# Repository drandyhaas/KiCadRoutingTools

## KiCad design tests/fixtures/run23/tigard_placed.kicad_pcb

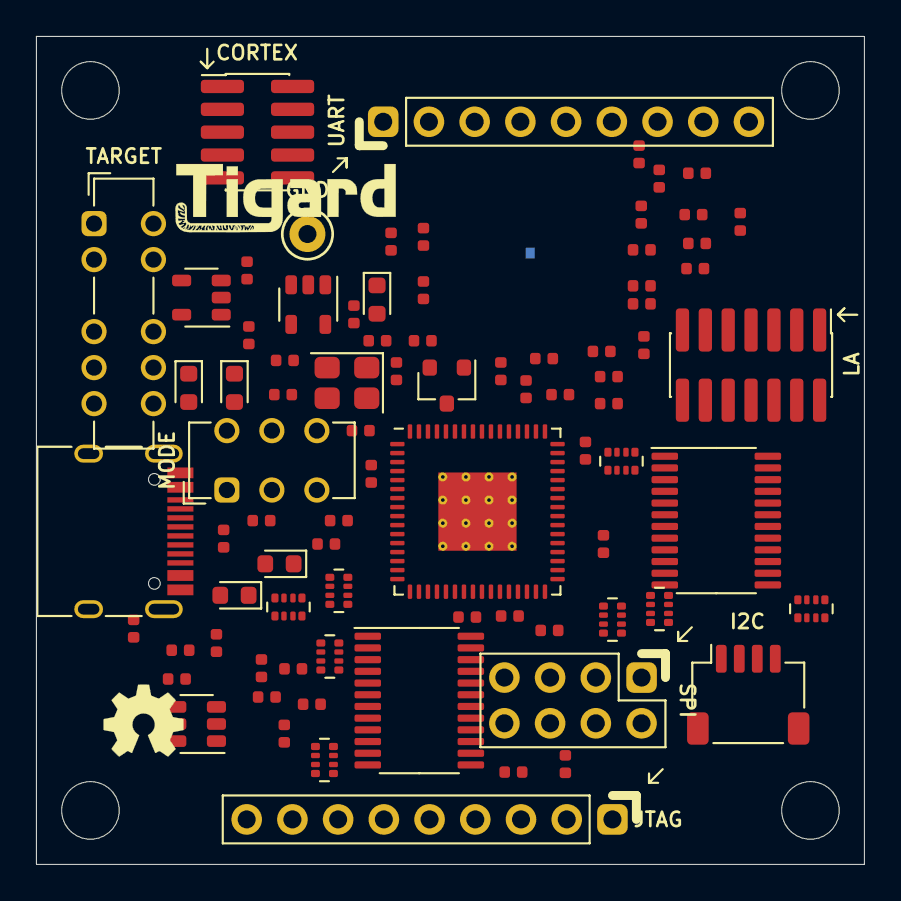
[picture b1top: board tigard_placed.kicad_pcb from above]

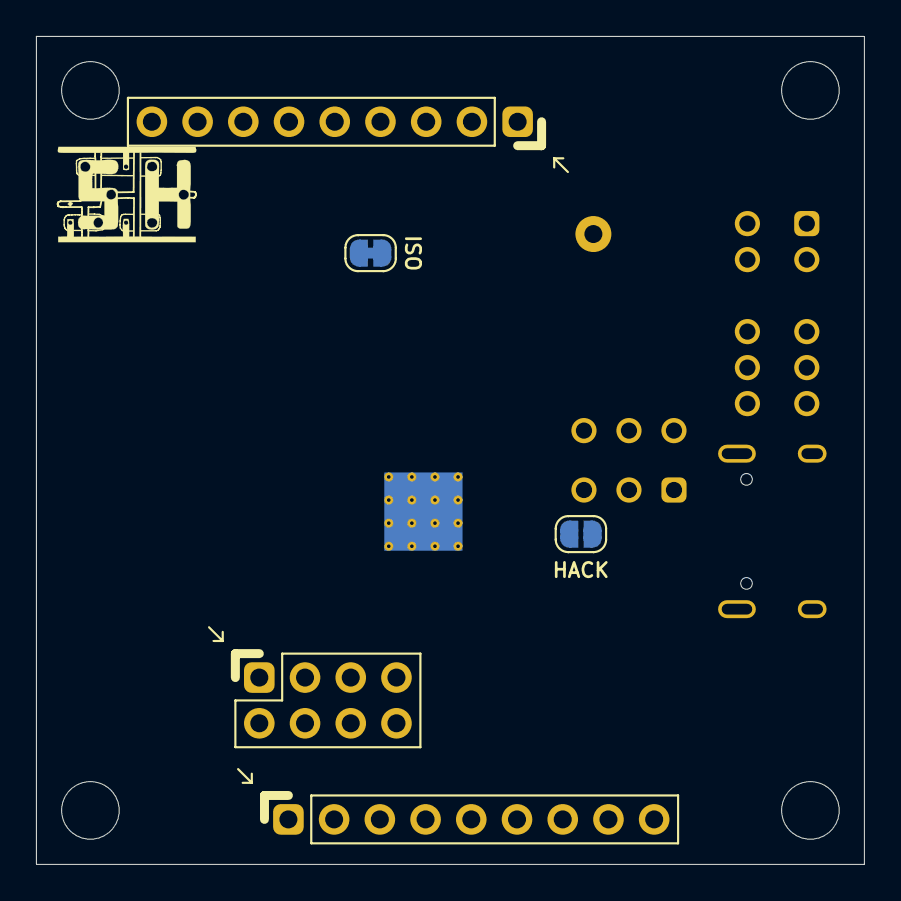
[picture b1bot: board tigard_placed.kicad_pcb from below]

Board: 4 copper layers, 46.0 x 46.0 mm, 91 parts (3 on the bottom side), 85 nets, no tracks yet.

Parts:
C1, C2, C3, C4, C6, C7, C9, C10: 2u2; C_0402_1005Metric
C5, C8, C11, C12, C13, C14, C15, C16, C17, C18, C19, C20, C21, C22, C26: 100n; C_0402_1005Metric
C23, C24: 30pF; C_0402_1005Metric
C25: NF; C_0402_1005Metric
D1, D4: YELLOW; LED_0603_1608Metric
D2: BLUE; LED_0603_1608Metric
D3, D5: GREEN; LED_0603_1608Metric
FB1, FB2, FB3: 600R, 0.5A; L_0402_1005Metric
H1, H2, H3, H4: MountingHole; MountingHole_3.2mm_M3_ISO7380
J1: USB_C_Receptacle_USB2.0; USB_C_Receptacle_HRO_TYPE-C-31-M-12
J2: JTAG; PinHeader_1x09_P2.54mm_Vertical
J3: UART; PinHeader_1x09_P2.54mm_Vertical
J4: SPI; PinHeader_2x04_P2.54mm_Vertical
J5: CORTEX; PinHeader_2x05_P1.27mm_Vertical_SMD
J6: LA; PinHeader_2x07_P1.27mm_Vertical_SMD
J7: I2C; JST_SH_SM04B-SRSS-TB_1x04-1MP_P1.00mm_Horizontal
JP1: ISO; SolderJumper-2_P1.3mm_Bridged_RoundedPad1.0x1.5mm
JP2: HACK; SolderJumper-2_P1.3mm_Open_RoundedPad1.0x1.5mm
LOGO1: Logo_Open_Hardware_Small; OSHW-Symbol_4.4x4mm_SilkScreen
LOGO2: Logo_SH; Securing_Hardware_Logo
Q1: BSH103; SOT-23_RoundRect
R1, R2: 5k1; R_0402_1005Metric
R3, R17: 1M; R_0402_1005Metric
R4, R5, R8, R9, R11, R16: 330; R_0402_1005Metric
R6: 12k, 1%; R_0402_1005Metric
R7, R10, R12, R13, R14, R18, R19, R20, R21, R24: 10k; R_0402_1005Metric
R15: 2.2k; R_0402_1005Metric
R22: 2k2; R_0402_1005Metric
RN1, RN2, RN7, RN8: 100k; R_Array_Convex_4x0402_RoundRect
RN3, RN4, RN5, RN6: 100; R_Array_Convex_4x0402_RoundRect
SW1: TARGET; SW_ALPS_SSSS224100_DP4T
SW2: MODE; SW_CuK_JS202011CQN_DPDT_Straight
TP1: GND; TestPoint_Keystone_5000-5004_Miniature
U1: AP7365-18; SOT-23-5_RoundRect
U2: AP7365-33; SOT-23-5_RoundRect
U3: FT2232HQ; QFN-64-1EP_9x9mm_P0.5mm_EP4.35x4.35mm_ThermalVias
U4: 93LC46BT-I/OT; SOT-23-6_RoundRect
U5, U6: SN74LVC8T245; TSSOP-24_4.4x7.8mm_P0.65mm
Y1: 12MHz; Crystal_SMD_3225-4Pin_3.2x2.5mm_RoundRect

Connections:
+1V8: C2.1, SW1.9, U1.5
+3V3: C4.1, C14.1, C15.1, C16.1, C17.1, C18.1, C19.1, C20.1, FB1.1, FB2.1, R4.1, R5.1, R7.1, R8.2, R9.2, R10.1, R11.2, R12.1, R13.1, R14.1, R18.1, RN1.1, RN1.2, RN1.3, RN1.4, RN2.1, RN2.2, RN2.3, RN2.4, SW1.7, U2.5, U3.20, U3.31, U3.42, U3.50, U3.56, U4.6, U5.1, U6.1
+5V: C1.1, C3.1, C26.1, FB3.1, SW1.6, U1.1, U1.3, U2.1, U2.3
/AD0: RN2.5, U3.16, U5.10
/AD1: RN5.1, U3.17
/AD2: RN2.6, U3.18, U5.9
/AD3: RN5.2, U3.19
/AD4: RN2.7, U3.21, U5.8
/AD5: RN5.3, U3.22
/AD6: RN5.4, U3.23
/BD0: RN1.8, U3.38, U5.3
/BD1: RN1.7, U3.39, U5.4
/BD2: RN6.1, U3.40
/BD3: RN1.6, U3.41, U5.5
/BD4: RN1.5, U3.43, U5.6
/BD5: R22.1, RN2.8, U3.44, U5.7
/BD6: RN6.2, U3.45
/BD7: R22.2, U3.46
/CIPO: J2.5, J4.3, J5.6, SW2.4
/CLK: J2.3, J4.6, J5.4, J6.1, J7.4, RN3.8
/COPI: J2.4, J4.8, J5.8, J6.2, J7.3, JP2.1, R16.2, RN3.7
/CORTEX_PIN2: J5.2, SW2.2
/CS: J2.6, J4.1, J6.4, RN3.6, SW2.1
/DI: J6.3, RN8.1, SW2.5, U6.17
/EECLK: R14.2, U3.62, U4.4
/EECS: R12.2, U3.63, U4.5
/EEDATA: R15.1, U3.61, U4.3
/ICE_CDONE: J2.9, J3.4, J6.8, RN7.1, RN8.2, U6.16, U6.21
/RXLED: D3.1, U3.29
/SWDIO: JP2.2, R16.1, SW2.3, SW2.6
/TXLED: D4.1, U3.30
/UART_TX: J3.3, J6.7, RN4.5
/USB_DN: J1.A7, J1.B7, U3.7
/USB_DP: J1.A6, J1.B6, U3.8
/VBUS: FB3.2, J1.A4, J1.A9, J1.B4, J1.B9
/VPHY: C5.1, C6.1, FB1.2, U3.4
/VPLL: C7.1, C8.1, FB2.2, U3.9
/xPB4: J2.7, J6.5, RN3.5
/xPB5: J2.8, J5.10, J6.6, RN4.8
/~ENABLE: D5.1, R10.2, U3.60, U5.22, U6.22
/~UART_CTS: J3.6, RN7.2, U6.20
/~UART_DCD: J3.9, RN7.4, U6.18
/~UART_DSR: J3.8, RN7.3, U6.19
/~UART_DTR: J3.7, RN4.7
/~UART_RTS: J3.5, RN4.6
GND: C1.2, C2.2, C3.2, C4.2, C5.2, C6.2, C7.2, C8.2, C9.2, C10.2, C11.2, C12.2, C13.2, C14.2, C15.2, C16.2, C17.2, C18.2, C19.2, C20.2, C21.2, C22.2, C23.2, C24.2, C25.1, C26.2, D1.1, J1.A1, J1.A12, J1.B1, J1.B12, J2.2, J3.2, J4.7, J5.3, J5.5, J5.9, J6.9, J6.10, J7.1, J7.MP, Q1.2, R1.1, R2.2, R3.1, R6.1, R17.2, R19.2, R24.1, TP1.1, U1.2, U2.2, U3.1, U3.5, U3.10, U3.11, U3.13, U3.15, U3.25, U3.35, U3.47, U3.51, U3.65, U4.2, U5.11, U5.12, U5.13, U6.11, U6.12, U6.13, Y1.2, Y1.4
unnamed: C23.1, U3.2, Y1.1
unnamed: C24.1, U3.3, Y1.3
unnamed: C25.2, J1.S1, R3.2
unnamed: D1.2, R4.2
unnamed: D2.1, Q1.3
unnamed: D2.2, R5.2
unnamed: D3.2, R8.1
unnamed: D4.2, R9.1
unnamed: D5.2, R11.1
unnamed: J1.A5, R1.2
unnamed: J1.B5, R2.1
unnamed: J4.4, R21.2
unnamed: J4.5, R20.1
unnamed: R6.2, U3.6
unnamed: R7.2, U3.14
unnamed: R13.2, R15.2, U4.1
unnamed: R18.2, U5.2
unnamed: R19.1, U6.2
unnamed: RN3.1, U5.21
unnamed: RN3.2, U5.20
unnamed: RN3.3, U5.19
unnamed: RN3.4, U5.18
unnamed: RN4.1, U5.17
unnamed: RN4.2, U5.16
unnamed: RN4.3, U5.15
unnamed: RN4.4, U5.14
unnamed: RN5.5, U6.6
unnamed: RN5.6, U6.5
unnamed: RN5.7, U6.4
unnamed: RN5.8, U6.3
unnamed: RN6.5, U6.10
unnamed: RN6.6, U6.9
unnamed: RN6.7, U6.8
unnamed: RN6.8, U6.7
unnamed: RN8.3, U6.15
unnamed: RN8.4, U6.14
VREF: C21.1, C22.1, JP1.2, Q1.1, R17.1, R24.2, RN7.5, RN7.6, RN7.7, RN7.8, RN8.5, RN8.6, RN8.7, RN8.8, SW1.8, U5.23, U5.24, U6.23, U6.24
VREG: C9.1, C10.1, C11.1, C12.1, C13.1, U3.12, U3.37, U3.49, U3.64
VTARGET: J2.1, J3.1, J4.2, J5.1, J7.2, JP1.1, R20.2, R21.1, SW1.10

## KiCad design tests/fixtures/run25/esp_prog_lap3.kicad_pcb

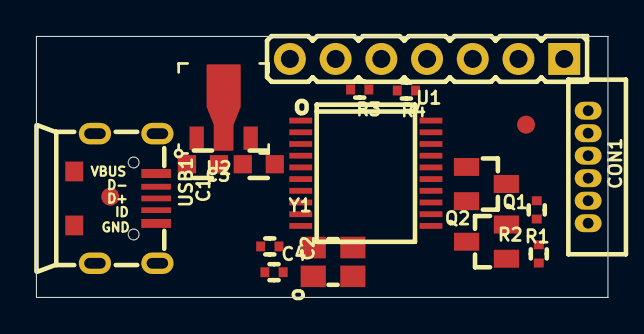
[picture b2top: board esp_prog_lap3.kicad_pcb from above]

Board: 2 copper layers, 31.8 x 14.5 mm, 18 parts (0 on the bottom side), 17 nets, no tracks yet.

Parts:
C1, C3: 2.2uF; C_0603_5MIL_DWS
C2, C4: 27pF; C_0402_5MIL_DWS
CON1: CON6; WU06SM
CON2: CON6; HN1x7
Q1, Q2: BC817-40(SOT23); SOT23
R1, R2: 1K; R_0402_5MIL_DWS
R3, R4: 100R; R_0402_5MIL_DWS
Ref*: Val**; Fiducial1x3_transp
Ref*#2: Val**; Fiducial1x3_transp
U1: CH340H/T; SSOP-20W
U2: ME6210-SOT89; SOT89
USB1: USB-uicro-B; USB-MICRO_MISB-SWMM-5B_LF
Y1: Q12MHz/20pF/10ppm/4P/3.2x2.5mm; TSX-3.2x2.5mm_GND(3)

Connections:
/+3.3V: C3.1, CON1.5, CON2.5, U1.5, U1.19, U2.3
/DCOM: CON1.2, CON2.2, Q1.3
/DTR: Q1.2, R2.2, U1.15
/D_N: U1.7, USB1.2
/D_P: U1.6, USB1.3
/EN: CON1.6, CON2.6, Q2.3
/RTS: Q2.2, R1.2, U1.16
/U0RXD: CON1.3, CON2.3, R3.1
/U0TXD: CON1.1, CON2.1, R4.1
GND: C1.2, C2.2, C3.2, C4.2, CON1.4, CON2.4, U1.8, U2.1, USB1.0, USB1.5, Y1.3
unnamed: C1.1, CON2.7, U2.2, USB1.1
unnamed: C2.1, U1.10, Y1.2
unnamed: C4.1, U1.9, Y1.1
unnamed: Q1.1, R1.1
unnamed: Q2.1, R2.1
unnamed: R3.2, U1.3
unnamed: R4.2, U1.4

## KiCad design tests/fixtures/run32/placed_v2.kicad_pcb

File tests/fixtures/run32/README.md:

# run32 fixtures: run 32's placed glasgow_revC

Copied from `repro/run32/` on `edgehero/KiCadRoutingTools@run32-assets`, the assets #1031 was filed against. That run's work directory (`wk/run32/`) is gitignored, so the test that pins #1031 on this board used to self-skip on every clone, and no machine had the board.

| file | what it is | sha256 (of the committed LF bytes) |
|---|---|---|
| `placed_v2.kicad_pcb` | glasgow_revC as run 32's placement left it, unrouted. Its rule area is a ~1.7 mm no-track, no-via band round the outline on F.Cu and B.Cu, with parts seated against it | `ce68fd39…6514` |
| `placed_v2.kicad_pro` | its project sibling (carries the DRC floor; never copy a board without it) | `488b5933…a714` |

Reader: `test_1031_keepout_run32_repro`. It checks that the pad-legality grader names exactly the parts whose pads no track can reach through that band (C89, D12, R11, R12, U14, U9), and that it does not name D4, D6, D11 or U31, whose pads sit near the band but connected when each net was routed alone on this board.

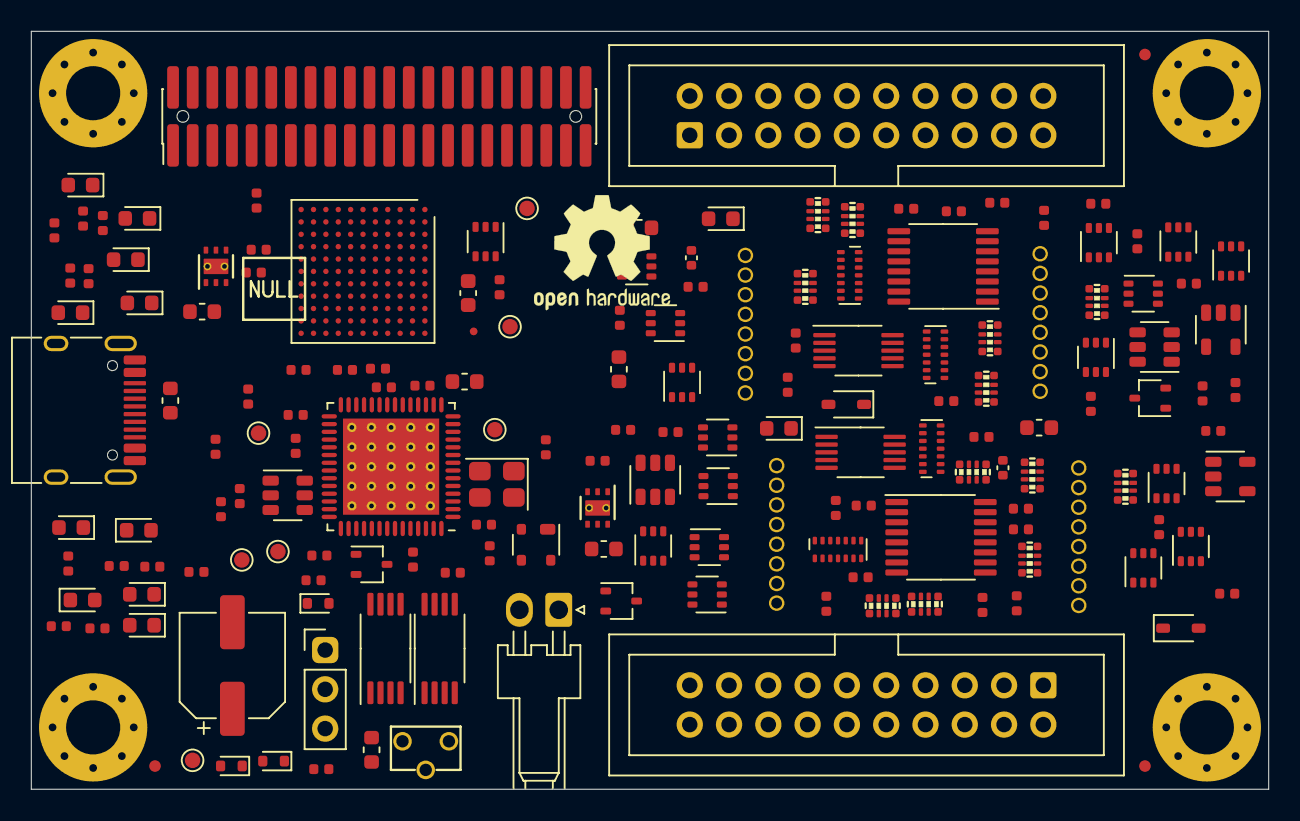
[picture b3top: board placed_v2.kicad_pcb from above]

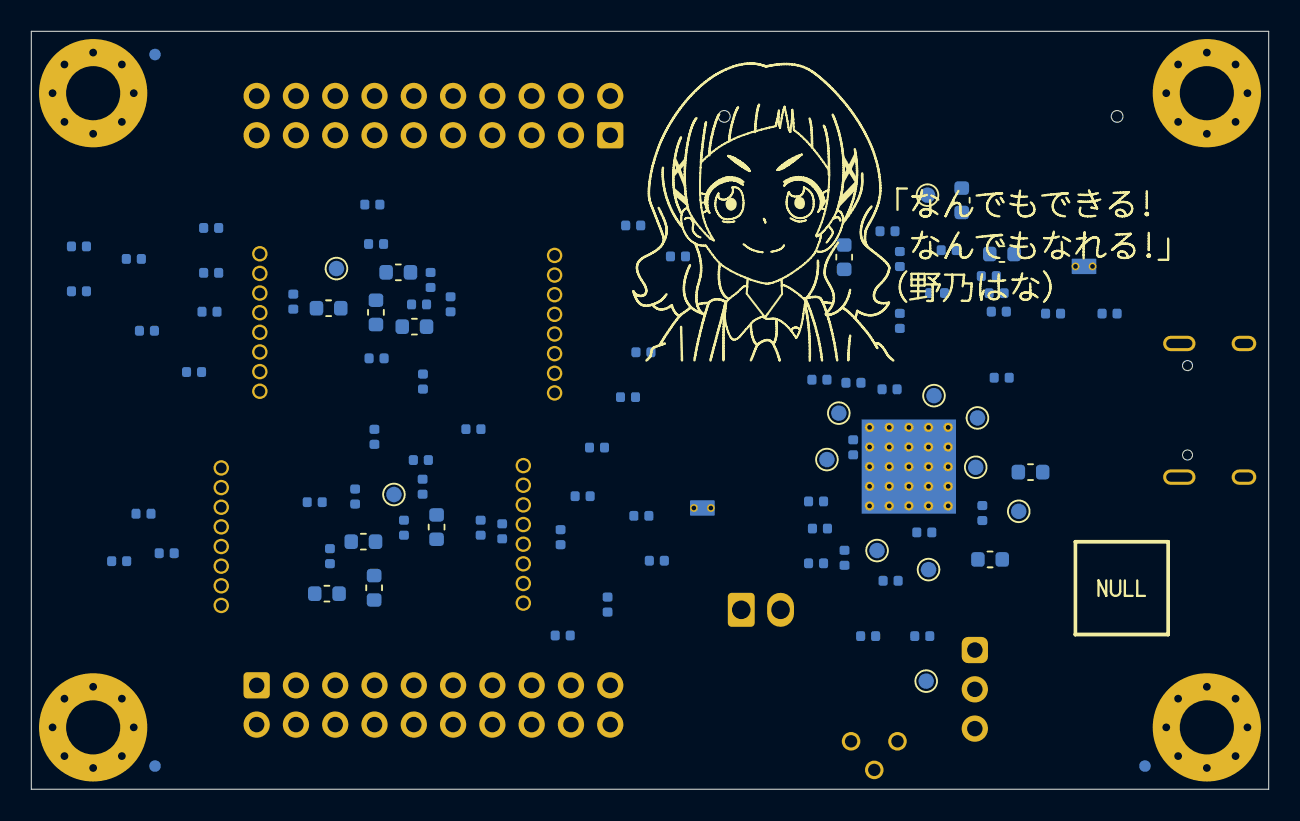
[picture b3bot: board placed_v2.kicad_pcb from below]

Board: 4 copper layers, 80.0 x 49.0 mm, 265 parts (93 on the bottom side), 226 nets, no tracks yet.

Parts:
C1, C14, C19, C26, C27, C28, C31, C53, C76, C80, C82, C83, C86, C92: 4u7; C_0603_1608Metric
C2, C3, C4, C5, C6, C7, C8, C9, C10, C13, C15, C16, C17, C18, C20, C21, C22, C23, C24, C25, C29, C30, C32, C33, C34, C35, C36, C37, C38, C39, C40, C41, C42, C43, C44, C45, C46, C47, C48, C49, C50, C51, C52, C54, C55, C56, C57, C58, C59, C60, C61, C62, C63, C64, C65, C66, C67, C68, C69, C70, C71, C72, C73, C74, C75, C77, C78, C79, C81, C84, C85, C88, C89: u1; C_0402_1005Metric
C11, C12: 9p; C_0402_1005Metric
C87: 150u; CP_Elec_6.3x5.9
C90, C91: 1n 50V C0G; C_0402_1005Metric
D1, D14, D15: GRN; LED_0603_1608Metric
D2, D8: WHT; LED_0603_1608Metric
D3, D6, D10: BLU; LED_0603_1608Metric
D4: ORA; LED_0603_1608Metric
D5: RED; LED_0603_1608Metric
D7, D9: PNK; LED_0603_1608Metric
D11, D12, D13: ESD5Z5.0T1G; D_SOD-523
D16, D17: CDSOD323-T36S; D_SOD-323
D18, D19: BAT54CW; SOT-323_SC-70
D20, D21, D22, D23: SP3012-06UTG; UDFN-14_3.5x1.35mm_P0.5mm
D24: BAT54AW; SOT-323_SC-70
FB1: 600R, 0.5A; L_0402_1005Metric
FID1, FID2, FID3, FID4, FID5, FID6: Fiducial_0.75mm_Mask1.5mm
FID8: Fiducial_0.5mm_Dia_1mm_Outer
J1: USB_C_USB2.0; USB_C_Receptacle_HRO_TYPE-C-31-M-12
J2, J3: IDC-Header_2x10_P2.54mm; IDC-Header_2x10_P2.54mm_Vertical
J4: Conn_01x02; Molex_KK-254_1x02_P2.54mm_Horizontal
J5: PinHeader_2x22_P1.27mm; PinHeader_2x22_P1.27mm_Vertical__SMD
J6, J7, J8, J9: Conn_01x08; PinSocket_1x08_P1.27mm_Vertical_DNP
J10: AUX; PinHeader_1x03_P2.54mm_Vertical
MK1, MK2, MK3, MK4: Mounting_Hole_PAD; MountingHole_3.5mm_Pad_Via_CrtYd
NONO_HANA: MECHOKKU; nono_hana_lines
R1, R2, R10, R11, R13, R14, R20, R21, R22, R23, R41, R42, R57, R58: 2k2; R_0402_1005Metric
R3, R4, R5, R9, R17: 100k; R_0402_1005Metric
R6, R8, R50, R51: DNP; R_0603_1608Metric_DNP
R7, R56: 0R33; R_0603_1608Metric
R12, R18, R19, R26, R36, R37, R44, R55: 10k; R_0402_1005Metric
R15, R16: 1k; R_0402_1005Metric
R24, R25, R30, R54: 4R7; R_0402_1005Metric
R27, R33: 49k9; R_0402_1005Metric
R28, R34: 59k; R_0402_1005Metric
R29, R35: 24k3; R_0402_1005Metric
R31, R32: 100R; R_0402_1005Metric
R38, R39, R43, R45: 47R; R_0402_1005Metric
R40: DNP; R_0402_1005Metric_DNP
R46, R47: 20k; R_0402_1005Metric
R48, R49: 0R15; R_0603_1608Metric
R52, R53: 5k1; R_0402_1005Metric
R59, R60: 470; R_0402_1005Metric
RN1, RN2, RN3, RN4, RN7, RN8, RN9, RN10: 33R; R_Array_Convex_4x0402
RN5, RN6, RN11, RN12: 10k; R_Array_Convex_4x0402
SW1: RST; SW_Tactile_SPST_Angled_TC-1109DE
TP1, TP8: 5V; TestPoint_Pad_D1.0mm
TP2, TP17: 1V2; TestPoint_Pad_D1.0mm
TP3, TP7, TP9: 3V3; TestPoint_Pad_D1.0mm
TP4, TP10: SDA; TestPoint_Pad_D1.0mm
TP5, TP11: SCL; TestPoint_Pad_D1.0mm
TP6: CLKREF; TestPoint_Pad_D1.0mm
TP12: GND; TestPoint_Pad_D1.0mm
TP13: VBUS; TestPoint_Pad_D1.0mm
TP14: USBGND; TestPoint_Pad_D1.0mm
TP15: USBDP; TestPoint_Pad_D1.0mm
TP16: USBDM; TestPoint_Pad_D1.0mm
TP18, TP19: VDAC; TestPoint_Pad_D1.0mm
U1: CY7C68013A-56LTX; Cypress_QFN-56-1EP_8x8mm_P0.5mm_EP6.22x6.22mm_ThermalVias
U2: CAT24M01X; TSSOP-8_4.4x3mm_P0.65mm
U3: BL24C256A-SFRC; TSSOP-8_4.4x3mm_P0.65mm
U4, U6, U9, U10, U11, U16, U17, U18, U22, U23, U24, U25, U26, U27, U28, U29, U32: SN74LVC1T45DCKR; SOT-363_SC-70-6
U5, U19: PCA6408APW; TSSOP-16_4.4x5mm_P0.65mm
U7: APX811-40UG-7; SOT-143
U8: TLV75533PDRVR; DFN-6-1EP_2x2mm_P0.65mm_EP1x1.6mm_ThermalVias
U12, U21: INA233; VSSOP-10_3x3mm_P0.5mm
U13, U20: DAC081C081CIMK; SOT-23-6
U14, U31: TPS73101DBV; SOT-23-5
U15: TPD3S014; SOT-23-6
U30: ICE40HX8K-BG121; BGA-121_9.0x9.0mm_Layout11x11_P0.8mm_Ball0.4mm_Pad0.35mm_NS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
U36: TLV73312PQDRVR; DFN-6-1EP_2x2mm_P0.65mm_EP1x1.6mm_ThermalVias
Y1: 24M; Crystal_SMD_3225-4Pin_3.2x2.5mm

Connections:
+1V2: C14.1, C18.1, C24.1, C25.1, C27.1, C77.1, R31.2, R32.2, TP2.1, TP17.1, U30.D4 (VCC), U30.D8 (VCC), U30.H4 (VCC), U30.H8 (VCC), U36.1 (OUT), U36.2 (NC)
+3V3: C1.1, C2.1, C3.1, C4.1, C5.1, C6.1, C7.1, C9.1, C10.1, C15.1, C17.1, C19.1, C20.1, C21.1, C22.1, C23.1, C28.1, C30.1, C32.1, C34.1, C35.1, C36.1, C37.1, C42.1, C43.1, C47.1, C48.1, C55.1, C56.1, C60.1, C61.1, C62.1, C63.1, C68.1, C69.1, C70.1, C71.1, C81.1, C84.1, C85.1, D24.1, J5.2, R1.2, R2.2, R4.1, R12.1, R17.2, R36.2, R37.2, R40.2, R44.2, TP3.1, TP9.1, U1.3 (AVCC), U1.7 (AVCC), U1.11 (VCC), U1.17 (VCC), U1.27 (VCC), U1.32 (VCC), U1.43 (VCC), U1.44 (WAKEUP), U1.55 (VCC), U2.2 (A1), U2.8 (VCC), U3.1 (A0), U3.8 (VCC), U4.1 (VCCA), U5.1 (VDD_I2C), U6.1 (VCCA), U8.1 (OUT), U8.2 (NC), U9.1 (VCCA), U10.1 (VCCA), U11.1 (VCCA), U12.2 (A0), U12.6 (VS), U13.2 (VA), U16.1 (VCCA), U17.1 (VCCA), U18.1 (VCCA), U19.1 (VDD_I2C), U20.2 (VA), U20.6 (ADR0), U21.6 (VS), U22.1 (VCCA), U23.1 (VCCA), U24.1 (VCCA), U25.1 (VCCA), U26.1 (VCCA), U27.1 (VCCA), U28.1 (VCCA), U29.1 (VCCA), U30.C10 (VPP_2V5), U30.D6 (VCCIO_0), U30.F8 (VCCIO_1), U30.H6 (VCCIO_2), U30.L11 (VCC_SPI), U32.1 (VCCA), U32.6 (VCCB)
+5V: C16.1, C26.2, C31.1, C45.1, C59.1, C82.1, C86.2, C87.1, TP1.1, TP8.1, U7.4 (VCC), U8.5 (NC), U8.6 (IN), U14.1 (IN), U15.4 (OUT), U31.1 (IN), U36.4 (EN), U36.5 (NC), U36.6 (IN)
/A0: U1.37 (PA4/FIOADDR0), U30.K3 (IOB_63)
/A1: U1.38 (PA5/FIOADDR1), U30.L2 (IOB_61)
/CC1: J1.A5 (CC1), R53.2
/CC2: J1.B5 (CC2), R52.2
/CLKIF: TP7.1, U1.13 (IFCLK), U30.K6 (IOB_82_GBIN4)
/CLKREF: TP6.1, U1.54 (CLKOUT), U30.D5 (IOT_212), U30.L5 (IOB_81_GBIN5)
/D0: U1.18 (PB0/FD0), U30.H7 (IOB_87)
/D1: U1.19 (PB1/FD1), U30.J7 (IOB_86)
/D2: U1.20 (PB2/FD2), U30.J9 (IOB_106_SDI)
/D3: U1.21 (PB3/FD3), U30.K10 (IOB_108_SS)
/D4: U1.22 (PB4/FD4), U30.L10 (IOB_107_SCK)
/D5: U1.23 (PB5/FD5), U30.K9 (IOB_105_SDO)
/D6: U1.24 (PB6/FD6), U30.L8 (IOB_103_CBSEL0)
/D7: U1.25 (PB7/FD7), U30.K7 (IOB_89)
/ENVA: R18.1, R47.1, R55.2, U1.45 (PD0/FD8)
/ENVB: R19.1, R26.2, R46.1, U1.51 (PD6/FD14)
/FLAGA: U1.29 (CTL0/FLAGA), U30.L7 (IOB_94)
/FLAGB: U1.30 (CTL1/FLAGB), U30.K5 (IOB_79)
/FLAGC: U1.31 (CTL2/FLAGC), U30.L4 (IOB_72)
/FLAGD: U1.40 (PA7/FLAGD/~SLCS), U30.J3 (IOB_57)
/FPGA_DONE: U1.36 (PA3/WU2), U30.K8 (CDONE)
/GNDPLL0: C76.2, C78.2, U30.L6 (GNDPLL0)
/GNDPLL1: C79.2, C80.2, U30.C5 (GNDPLL1)
/IO_Banks/DA0: U4.5 (DIR), U30.C7 (IOT_191)
/IO_Banks/DA1: U11.5 (DIR), U30.C8 (IOT_179)
/IO_Banks/DA2: U6.5 (DIR), U30.D7 (IOT_181)
/IO_Banks/DA3: U16.5 (DIR), U30.A7 (IOT_192)
/IO_Banks/DA4: U9.5 (DIR), U30.B8 (IOT_177)
/IO_Banks/DA5: U17.5 (DIR), U30.A8 (IOT_190)
/IO_Banks/DA6: U10.5 (DIR), U30.B9 (IOT_174)
/IO_Banks/DA7: U18.5 (DIR), U30.A9 (IOT_178)
/IO_Banks/DB0: U22.5 (DIR), U30.F9 (IOR_137)
/IO_Banks/DB1: U26.5 (DIR), U30.G11 (IOR_129)
/IO_Banks/DB2: U23.5 (DIR), U30.G10 (IOR_120)
/IO_Banks/DB3: U27.5 (DIR), U30.H11 (IOR_119)
/IO_Banks/DB4: U24.5 (DIR), U30.H10 (IOR_116)
/IO_Banks/DB5: U28.5 (DIR), U30.J11 (IOR_114)
/IO_Banks/DB6: U25.5 (DIR), U30.J10 (IOR_117)
/IO_Banks/DB7: U29.5 (DIR), U30.K11 (IOR_115)
/IO_Banks/IO_Buffer_A/ISNS_H: R8.2, R30.1, R49.1, R51.1, R56.2
/IO_Banks/IO_Buffer_A/P0: J9.1, RN11.5 (R4.2), U19.4 (P0)
/IO_Banks/IO_Buffer_A/P1: J9.2, RN11.6 (R3.2), U19.5 (P1)
/IO_Banks/IO_Buffer_A/P2: J9.3, RN11.7 (R2.2), U19.6 (P2)
/IO_Banks/IO_Buffer_A/P3: J9.4, RN11.8 (R1.2), U19.7 (P3)
/IO_Banks/IO_Buffer_A/P4: J9.5, RN12.5 (R4.2), U19.9 (P4)
/IO_Banks/IO_Buffer_A/P5: J9.6, RN12.6 (R3.2), U19.10 (P5)
/IO_Banks/IO_Buffer_A/P6: J9.7, RN12.7 (R2.2), U19.11 (P6)
/IO_Banks/IO_Buffer_A/P7: J9.8, RN12.8 (R1.2), U19.12 (P7)
/IO_Banks/IO_Buffer_A/VDAC: R33.1, TP19.1, U20.1 (VOUT)
/IO_Banks/IO_Buffer_A/VFB: R33.2, R34.1, R35.2, U31.4 (FB)
/IO_Banks/IO_Buffer_A/VIO_EN: D19.2, R55.1, U31.3 (EN)
/IO_Banks/IO_Buffer_A/VSENSE: D17.1 (K), J2.1, R60.2
/IO_Banks/IO_Buffer_A/X0: RN7.8 (R1.2), U4.3 (A)
/IO_Banks/IO_Buffer_A/X1: RN7.7 (R2.2), U11.3 (A)
/IO_Banks/IO_Buffer_A/X2: RN7.6 (R3.2), U6.3 (A)
/IO_Banks/IO_Buffer_A/X3: RN7.5 (R4.2), U16.3 (A)
/IO_Banks/IO_Buffer_A/X4: RN8.8 (R1.2), U9.3 (A)
/IO_Banks/IO_Buffer_A/X5: RN8.7 (R2.2), U17.3 (A)
/IO_Banks/IO_Buffer_A/X6: RN8.6 (R3.2), U10.3 (A)
/IO_Banks/IO_Buffer_A/X7: RN8.5 (R4.2), U18.3 (A)
/IO_Banks/IO_Buffer_A/Y0: RN9.1 (R1.1), U4.4 (B)
/IO_Banks/IO_Buffer_A/Y1: RN9.2 (R2.1), U11.4 (B)
/IO_Banks/IO_Buffer_A/Y2: RN9.3 (R3.1), U6.4 (B)
/IO_Banks/IO_Buffer_A/Y3: RN9.4 (R4.1), U16.4 (B)
/IO_Banks/IO_Buffer_A/Y4: RN10.1 (R1.1), U9.4 (B)
/IO_Banks/IO_Buffer_A/Y5: RN10.2 (R2.1), U17.4 (B)
/IO_Banks/IO_Buffer_A/Y6: RN10.3 (R3.1), U10.4 (B)
/IO_Banks/IO_Buffer_A/Y7: RN10.4 (R4.1), U18.4 (B)
/IO_Banks/IO_Buffer_A/Z0: D22.4 (N/C), D22.11 (Ch4), J2.3, J8.1, RN9.8 (R1.2), RN11.4 (R4.1)
/IO_Banks/IO_Buffer_A/Z1: D22.3 (N/C), D22.12 (Ch3), J2.5, J8.2, RN9.7 (R2.2), RN11.3 (R3.1)
/IO_Banks/IO_Buffer_A/Z2: D22.2 (N/C), D22.13 (Ch2), J2.7, J8.3, RN9.6 (R3.2), RN11.2 (R2.1)
/IO_Banks/IO_Buffer_A/Z3: D22.1 (N/C), D22.14 (Ch1), J2.9, J8.4, RN9.5 (R4.2), RN11.1 (R1.1)
/IO_Banks/IO_Buffer_A/Z4: D23.4 (N/C), D23.11 (Ch4), J2.11, J8.5, RN10.8 (R1.2), RN12.4 (R4.1)
/IO_Banks/IO_Buffer_A/Z5: D23.3 (N/C), D23.12 (Ch3), J2.13, J8.6, RN10.7 (R2.2), RN12.3 (R3.1)
/IO_Banks/IO_Buffer_A/Z6: D23.2 (N/C), D23.13 (Ch2), J2.15, J8.7, RN10.6 (R3.2), RN12.2 (R2.1)
/IO_Banks/IO_Buffer_A/Z7: D23.1 (N/C), D23.14 (Ch1), J2.17, J8.8, RN10.5 (R4.2), RN12.1 (R1.1)
/IO_Banks/IO_Buffer_B/ISNS_H: R6.2, R7.2, R24.1, R48.1, R50.1
/IO_Banks/IO_Buffer_B/P0: J7.1, RN5.5 (R4.2), U5.4 (P0)
/IO_Banks/IO_Buffer_B/P1: J7.2, RN5.6 (R3.2), U5.5 (P1)
/IO_Banks/IO_Buffer_B/P2: J7.3, RN5.7 (R2.2), U5.6 (P2)
/IO_Banks/IO_Buffer_B/P3: J7.4, RN5.8 (R1.2), U5.7 (P3)
/IO_Banks/IO_Buffer_B/P4: J7.5, RN6.5 (R4.2), U5.9 (P4)
/IO_Banks/IO_Buffer_B/P5: J7.6, RN6.6 (R3.2), U5.10 (P5)
/IO_Banks/IO_Buffer_B/P6: J7.7, RN6.7 (R2.2), U5.11 (P6)
/IO_Banks/IO_Buffer_B/P7: J7.8, RN6.8 (R1.2), U5.12 (P7)
/IO_Banks/IO_Buffer_B/VDAC: R27.1, TP18.1, U13.1 (VOUT)
/IO_Banks/IO_Buffer_B/VFB: R27.2, R28.1, R29.2, U14.4 (FB)
/IO_Banks/IO_Buffer_B/VIO_EN: D18.2, R26.1, U14.3 (EN)
/IO_Banks/IO_Buffer_B/VSENSE: D16.1 (K), J3.1, R59.2
/IO_Banks/IO_Buffer_B/X0: RN1.8 (R1.2), U22.3 (A)
/IO_Banks/IO_Buffer_B/X1: RN1.7 (R2.2), U26.3 (A)
/IO_Banks/IO_Buffer_B/X2: RN1.6 (R3.2), U23.3 (A)
/IO_Banks/IO_Buffer_B/X3: RN1.5 (R4.2), U27.3 (A)
/IO_Banks/IO_Buffer_B/X4: RN2.8 (R1.2), U24.3 (A)
/IO_Banks/IO_Buffer_B/X5: RN2.7 (R2.2), U28.3 (A)
/IO_Banks/IO_Buffer_B/X6: RN2.6 (R3.2), U25.3 (A)
/IO_Banks/IO_Buffer_B/X7: RN2.5 (R4.2), U29.3 (A)
/IO_Banks/IO_Buffer_B/Y0: RN3.1 (R1.1), U22.4 (B)
/IO_Banks/IO_Buffer_B/Y1: RN3.2 (R2.1), U26.4 (B)
/IO_Banks/IO_Buffer_B/Y2: RN3.3 (R3.1), U23.4 (B)
/IO_Banks/IO_Buffer_B/Y3: RN3.4 (R4.1), U27.4 (B)
/IO_Banks/IO_Buffer_B/Y4: RN4.1 (R1.1), U24.4 (B)
/IO_Banks/IO_Buffer_B/Y5: RN4.2 (R2.1), U28.4 (B)
/IO_Banks/IO_Buffer_B/Y6: RN4.3 (R3.1), U25.4 (B)
/IO_Banks/IO_Buffer_B/Y7: RN4.4 (R4.1), U29.4 (B)
/IO_Banks/IO_Buffer_B/Z0: D20.4 (N/C), D20.11 (Ch4), J3.3, J6.1, RN3.8 (R1.2), RN5.4 (R4.1)
/IO_Banks/IO_Buffer_B/Z1: D20.3 (N/C), D20.12 (Ch3), J3.5, J6.2, RN3.7 (R2.2), RN5.3 (R3.1)
/IO_Banks/IO_Buffer_B/Z2: D20.2 (N/C), D20.13 (Ch2), J3.7, J6.3, RN3.6 (R3.2), RN5.2 (R2.1)
/IO_Banks/IO_Buffer_B/Z3: D20.1 (N/C), D20.14 (Ch1), J3.9, J6.4, RN3.5 (R4.2), RN5.1 (R1.1)
/IO_Banks/IO_Buffer_B/Z4: D21.4 (N/C), D21.11 (Ch4), J3.11, J6.5, RN4.8 (R1.2), RN6.4 (R4.1)
/IO_Banks/IO_Buffer_B/Z5: D21.3 (N/C), D21.12 (Ch3), J3.13, J6.6, RN4.7 (R2.2), RN6.3 (R3.1)
/IO_Banks/IO_Buffer_B/Z6: D21.2 (N/C), D21.13 (Ch2), J3.15, J6.7, RN4.6 (R3.2), RN6.2 (R2.1)
/IO_Banks/IO_Buffer_B/Z7: D21.1 (N/C), D21.14 (Ch1), J3.17, J6.8, RN4.5 (R4.2), RN6.1 (R1.1)
/IO_Banks/QA0: RN7.1 (R1.1), U30.A1 (IOT_225)
/IO_Banks/QA1: RN7.2 (R2.1), U30.A2 (IOT_222)
/IO_Banks/QA2: RN7.3 (R3.1), U30.B3 (IOT_221)
/IO_Banks/QA3: RN7.4 (R4.1), U30.A3 (IOT_223)
/IO_Banks/QA4: RN8.1 (R1.1), U30.B5 (IOT_208), U30.B6 (IOT_198_GBIN0)
/IO_Banks/QA5: RN8.2 (R2.1), U30.A4 (IOT_211)
/IO_Banks/QA6: RN8.3 (R3.1), U30.A6 (IOT_206), U30.B7 (IOT_197_GBIN1)
/IO_Banks/QA7: RN8.4 (R4.1), U30.A5 (IOT_207)
/IO_Banks/QB0: RN1.1 (R1.1), U30.B11 (IOR_161)
/IO_Banks/QB1: RN1.2 (R2.1), U30.C11 (IOR_160)
/IO_Banks/QB2: RN1.3 (R3.1), U30.D10 (IOR_154)
/IO_Banks/QB3: RN1.4 (R4.1), U30.D11 (IOR_152)
/IO_Banks/QB4: RN2.1 (R1.1), U30.E10 (IOR_141_GBIN2)
/IO_Banks/QB5: RN2.2 (R2.1), U30.E11 (IOR_148)
/IO_Banks/QB6: RN2.3 (R3.1), U30.F11 (IOR_140_GBIN3)
/IO_Banks/QB7: RN2.4 (R4.1), U30.F10 (IOR_136)
/IO_Banks/U1: R11.1, U30.G9 (IOR_128)
/IO_Banks/U2: R20.1, U30.G8 (IOR_118)
/IO_Banks/U3: R21.1, U30.E9 (IOR_144)
/IO_Banks/U4: R22.1, U30.D9 (IOR_147)
/IO_Banks/U5: R23.1, U30.E8 (IOR_146)
/IO_Banks/VIOA: C38.1, C39.1, C40.1, C41.1, C49.1, C50.1, C51.1, C52.1, C54.1, C57.1, C83.1, D22.6 (N/C), D22.7 (N/C), D22.8 (Ch6), D22.9 (Ch5), J2.2, R34.2, R42.2, R49.2, R51.2, R54.1, R58.2, U4.6 (VCCB), U6.6 (VCCB), U9.6 (VCCB), U10.6 (VCCB), U11.6 (VCCB), U16.6 (VCCB), U17.6 (VCCB), U18.6 (VCCB), U19.16 (VDD_P)
/IO_Banks/VIOB: C29.1, C46.1, C53.1, C64.1, C65.1, C66.1, C67.1, C72.1, C73.1, C74.1, C75.1, D20.6 (N/C), D20.7 (N/C), D20.8 (Ch6), D20.9 (Ch5), J3.2, R25.1, R28.2, R41.2, R48.2, R50.2, R57.2, U5.2 (ADDR), U5.16 (VDD_P), U22.6 (VCCB), U23.6 (VCCB), U24.6 (VCCB), U25.6 (VCCB), U26.6 (VCCB), U27.6 (VCCB), U28.6 (VCCB), U29.6 (VCCB)
/IO_Banks/VIO_AUX: C33.1, C92.1, J5.44, U30.E4 (VCCIO_3), U30.G4 (VCCIO_3)
/IO_Banks/Z0_N: J5.41, U30.B2 (IOL_2B)
/IO_Banks/Z0_P: J5.39, U30.B1 (IOL_2A)
/IO_Banks/Z1_N: J5.38, U30.C3 (IOL_4B)
/IO_Banks/Z1_P: J5.40, U30.C4 (IOL_4A)
/IO_Banks/Z2_N: J5.33, U30.C1 (IOL_5B)
/IO_Banks/Z2_P: J5.35, U30.C2 (IOL_5A)
/IO_Banks/Z3_N: J5.29, U30.D1 (IOL_8B)
/IO_Banks/Z3_P: J5.27, U30.E1 (IOL_8A)
/IO_Banks/Z4_N: J5.34, U30.D3 (IOL_9B)
/IO_Banks/Z4_P: J5.32, U30.D2 (IOL_9A)
/IO_Banks/Z5_N: J5.26, U30.E3 (IOL_10B)
/IO_Banks/Z5_P: J5.28, U30.E2 (IOL_10A)
/IO_Banks/Z6_N: J5.23, U30.F2 (IOL_12B)
/IO_Banks/Z6_P: J5.21, U30.F1 (IOL_12A)
/IO_Banks/Z7_N: J5.20, U30.F3 (IOL_13B_GBIN7)
/IO_Banks/Z7_P: J5.22, U30.F4 (IOL_13A)
/IO_Banks/Z8_N: J5.17, U30.G2 (IOL_14B)
/IO_Banks/Z8_P: J5.15, U30.G1 (IOL_14A_GBIN6)
/IO_Banks/Z9_N: J5.14, U30.H3 (IOL_17B)
/IO_Banks/Z9_P: J5.16, U30.G3 (IOL_17A)
/IO_Banks/Z10_N: J5.11, U30.H2 (IOL_18B)
/IO_Banks/Z10_P: J5.9, U30.H1 (IOL_18A)
/IO_Banks/Z11_N: J5.3, U30.K1 (IOL_23B)
/IO_Banks/Z11_P: J5.5, U30.J1 (IOL_23A)
/IO_Banks/Z12_N: J5.10, U30.J2 (IOL_25B)
/IO_Banks/Z12_P: J5.8, U30.K2 (IOL_25A)
/IO_Banks/~SYNC: D11.1 (K), J4.2, R38.1, R44.1
/LED_ACT: R15.1, U1.49 (PD4/FD12)
/LED_CY: R13.1, U1.47 (PD2/FD10)
/LED_ERR: R16.1, U1.50 (PD5/FD13)
/LED_FPGA: R14.1, U1.48 (PD3/FD11)
/OE: U1.35 (PA2/SLOE), U30.L3 (IOB_71)
/PKTEND: U1.39 (PA6/PKTEND), U30.L1 (IOB_56)
/RD: U1.1 (RDY0/SLRD), U30.J5 (IOB_78)
/SCL: R2.1, TP5.1, TP11.1, U1.15 (SCL), U2.6 (SCL), U3.6 (SCL), U5.14 (SCL), U12.5 (SCL), U13.5 (SCL), U19.14 (SCL), U20.5 (SCL), U21.5 (SCL), U30.H9 (IOB_104_CBSEL1)
/SDA: R1.1, TP4.1, TP10.1, U1.16 (SDA), U2.5 (SDA), U3.5 (SDA), U5.15 (SDA), U12.4 (SDA), U13.4 (SDA), U19.15 (SDA), U20.4 (SDA), U21.4 (SDA), U30.J8 (IOB_91)
/SHLD: C13.1, J1.S1 (SHIELD), R3.1
/USB_N: J1.A7 (D-), J1.B7 (D-), TP16.1, U1.9 (D-), U15.5 (D1)
/USB_P: J1.A6 (D+), J1.B6 (D+), TP15.1, U1.8 (D+), U15.6 (D2)
/VCCPLL0: C76.1, C78.1, R31.1, U30.J6 (VCCPLL0)
/VCCPLL1: C79.1, C80.1, R32.1, U30.C6 (VCCPLL1)
/VUSB: C8.1, FB1.2, U15.1 (EN), U15.3 (IN)
/WR: U1.2 (RDY1/SLWR), U30.J4 (IOB_64)
/XTALIN: C12.1, U1.5 (XTALIN), Y1.1
/XTALOUT: C11.1, U1.4 (XTALOUT), Y1.3
/xVBUS: FB1.1, J1.A4 (VBUS), J1.A9 (VBUS), J1.B4 (VBUS), J1.B9 (VBUS), TP13.1
/~ALERT: D18.1, D19.1, R17.1, U1.33 (PA0/~INT0), U30.K4 (IOB_73)
/~CY_RESET: C88.1, D24.3, R5.2, U1.42 (~RESET)
/~FPGA_RESET: R9.2, U1.34 (PA1/~INT1), U30.L9 (~CRESET)
/~MR: C89.1, SW1.2, U7.3 (~MR)
GND: C1.2, C2.2, C3.2, C4.2, C5.2, C6.2, C7.2, C8.2, C9.2, C10.2, C11.2, C12.2, C13.2, C14.2, C15.2, C16.2, C17.2, C18.2, C19.2, C20.2, C21.2, C22.2, C23.2, C24.2, C25.2, C26.1, C27.2, C28.2, C29.2, C30.2, C31.2, C32.2, C33.2, C34.2, C35.2, C36.2, C37.2, C38.2, C39.2, C40.2, C41.2, C42.2, C43.2, C45.2, C46.2, C47.2, C48.2, C49.2, C50.2, C51.2, C52.2, C53.2, C54.2, C55.2, C56.2, C57.2, C59.2, C60.2, C61.2, C62.2, C63.2, C64.2, C65.2, C66.2, C67.2, C68.2, C69.2, C70.2, C71.2, C72.2, C73.2, C74.2, C75.2, C77.2, C81.2, C82.2, C83.2, C84.2, C85.2, C86.1, C87.2, C88.2, C89.2, C90.1, C91.1, C92.2, D1.1 (K), D2.1 (K), D3.1 (K), D4.1 (K), D5.1 (K), D6.1 (K), D7.1 (K), D8.1 (K), D9.1 (K), D10.1 (K), D11.2 (A), D12.2 (A), D13.2 (A), D14.1 (K), D15.1 (K), D16.2 (A), D17.2 (A), D20.5 (N/C), D20.10 (GND), D21.5 (N/C), D21.10 (GND), D22.5 (N/C), D22.10 (GND), D23.5 (N/C), D23.10 (GND), J1.A1 (GND), J1.A12 (GND), J1.B1 (GND), J1.B12 (GND), J2.4, J2.6, J2.8, J2.10, J2.12, J2.14, J2.16, J2.18, J3.4, J3.6, J3.8, J3.10, J3.12, J3.14, J3.16, J3.18, J4.1, J5.1, J5.4, J5.6, J5.7, J5.12, J5.13, J5.18, J5.19, J5.24, J5.25, J5.30, J5.31, J5.36, J5.37, J5.42, J5.43, J10.1, MK1.1, MK2.1, MK3.1, MK4.1, R3.2, R9.1, R10.2, R18.2, R19.2, R29.1, R35.1, R41.1, R42.1, R52.1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
unnamed: D1.2 (A), R12.2
unnamed: D2.2 (A), R13.2
unnamed: D3.2 (A), R14.2
unnamed: D4.2 (A), R15.2
unnamed: D5.2 (A), R16.2
unnamed: D6.2 (A), R11.2
unnamed: D7.2 (A), R20.2
unnamed: D8.2 (A), R21.2
unnamed: D9.2 (A), R22.2
unnamed: D10.2 (A), R23.2
unnamed: D12.1 (K), J10.2, R39.1
unnamed: D13.1 (K), J10.3, R43.1
unnamed: D14.2 (A), R46.2
unnamed: D15.2 (A), R47.2
unnamed: R4.2, R5.1
unnamed: R40.1, U3.2 (A1)
unnamed: R36.1, U5.3 (~RESET)
unnamed: D24.2, U7.2 (~RESET), U8.4 (EN)
unnamed: C90.2, R59.1, U12.8 (Vbus)
unnamed: C44.2, R24.2, U12.10 (Vin+)
unnamed: C44.1, R25.2, U12.9 (Vin-)
unnamed: D18.3, U12.3 (~Alert)
unnamed: R6.1, R7.1, U14.5 (OUT)
unnamed: R37.1, U19.3 (~RESET)
unnamed: C91.2, R60.1, U21.8 (Vbus)
unnamed: C58.2, R30.2, U21.10 (Vin+)
unnamed: C58.1, R54.2, U21.9 (Vin-)
unnamed: D19.3, U21.3 (~Alert)
unnamed: R45.2, U30.A11 (IOT_168)
unnamed: R39.2, U30.A10 (IOT_170)
unnamed: R43.2, U30.C9 (IOT_172)
unnamed: R10.1, U30.B4 (IOT_219), U32.5 (DIR)
unnamed: R8.1, R56.1, U31.5 (OUT)
unnamed: R45.1, U32.3 (A)
unnamed: R38.2, U32.4 (B)

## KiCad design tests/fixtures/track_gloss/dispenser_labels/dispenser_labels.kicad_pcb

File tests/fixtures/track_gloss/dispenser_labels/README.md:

# `dispenser_labels` Track Gloss regression fixture

This fixture is a byte-for-byte copy of the KiCad 10 board, project, and
design-rule files supplied for the Track Gloss investigation. The source files
were copied from the local `dispenser` project on 2026-08-24; tests never save
or modify that source project.

SHA-256 fingerprints:

- `dispenser_labels.kicad_pcb`: `B276B421666B955944EFBCEE579A0D8273385DDD8E8BFBF2F41D41612518F9B1`
- `dispenser_labels.kicad_pro`: `0D9CD2BB27C0DDEE20FF389ED4927FE31DF053958787F500C5627E5AFD6B9BE0`
- `dispenser_labels.kicad_dru`: `18412D66DC4BDD8A958FFBB22BCF48804675197E902B5B15607AA16E1D38B591`

Run the real-board pattern replay with KiCad's bundled Python:

```text
D:\kicad\bin\python.exe tests\run_track_gloss_patterns.py
```

The replay loads a fresh in-memory board for every accepted modification and
never writes a PCB file.

It also treats all 706 straight tracks as one simultaneous selection. The
expected deterministic result is 4.341542 mm of copper saved and a net
reduction of 38 segments (100 removed, 62 added), invariant under board,
reverse, ascending-net, descending-net, and shuffled input orders.

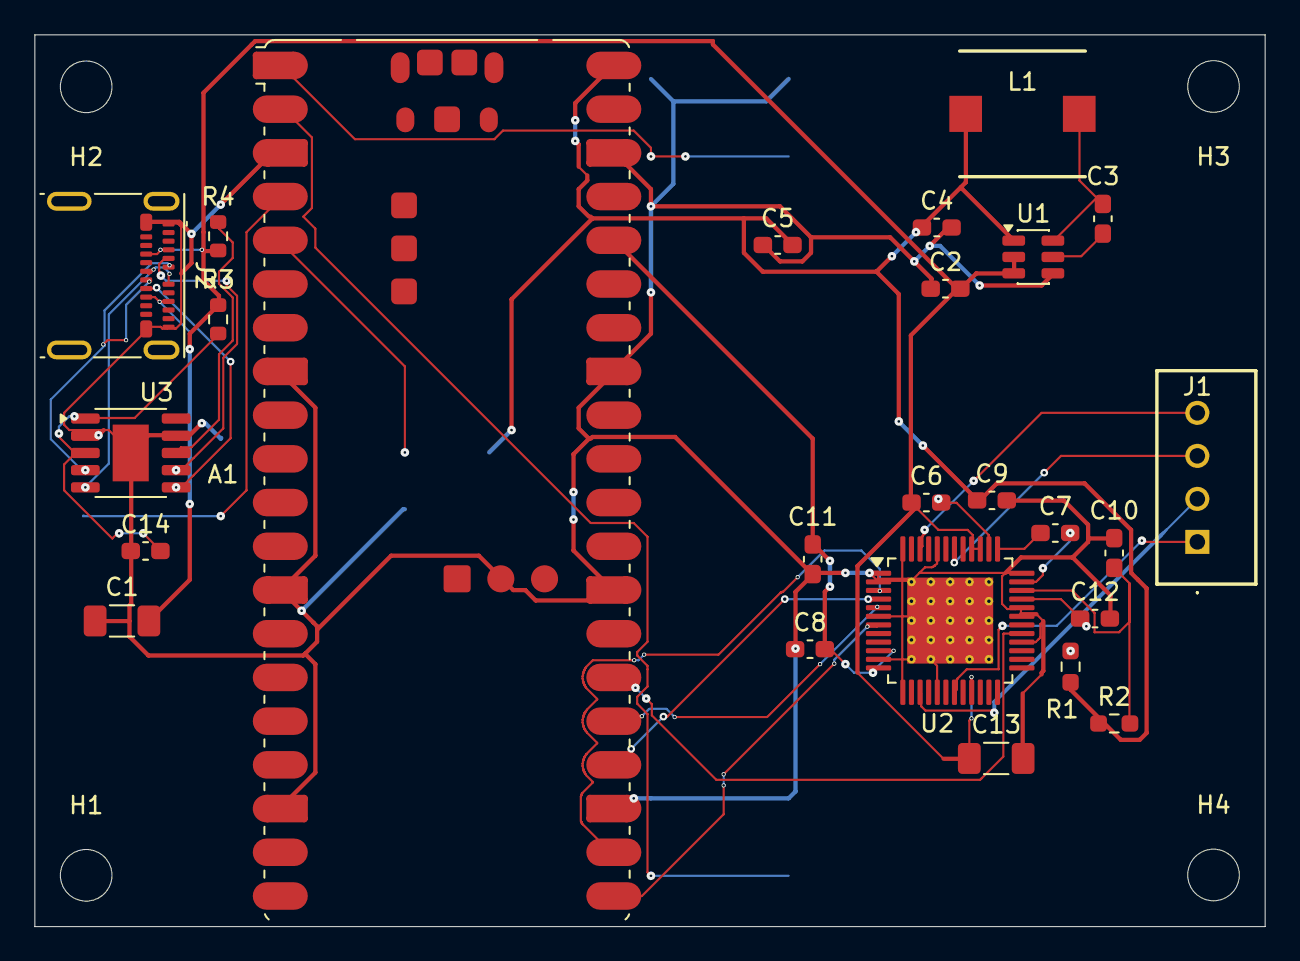
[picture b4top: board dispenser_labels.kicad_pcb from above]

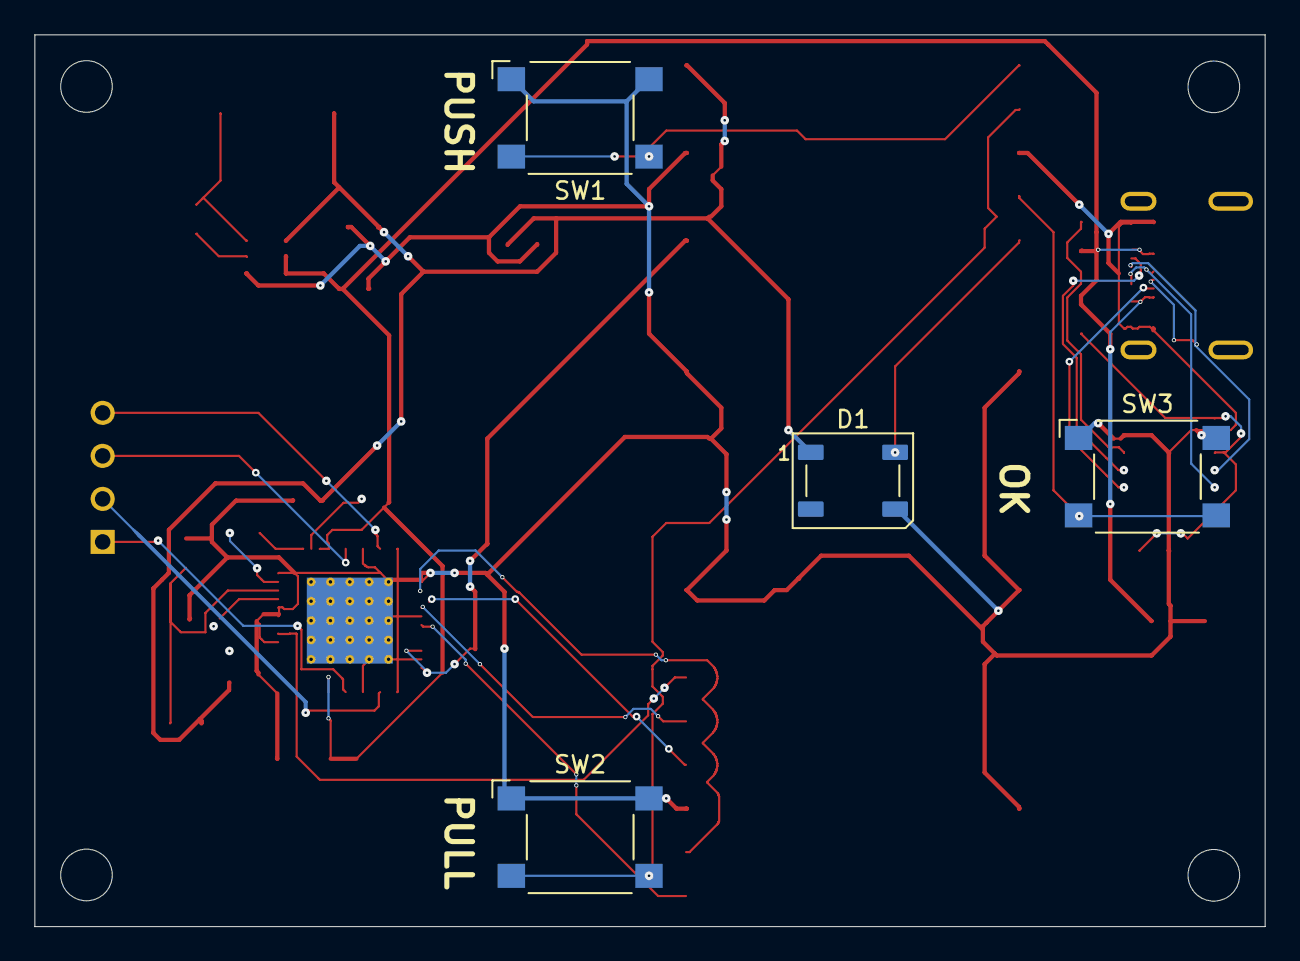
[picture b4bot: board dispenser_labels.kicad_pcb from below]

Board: 2 copper layers, 71.5 x 51.8 mm, 33 parts (4 on the bottom side), 31 nets.

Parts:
A1: RaspberryPi_Pico_W; RaspberryPi_Pico_W_SMD
C1, C13: 22uF; C_1206_3216Metric_Pad1.33x1.80mm_HandSolder
C2, C3, C4, C5, C6, C8, C9, C11, C12, C14: 100nF; C_0603_1608Metric_Pad1.08x0.95mm_HandSolder
C7: 22nF; C_0603_1608Metric_Pad1.08x0.95mm_HandSolder
C10: 480nF; C_0603_1608Metric_Pad1.08x0.95mm_HandSolder
D1: WS2812B; LED_WS2812B_PLCC4_5.0x5.0mm_P3.2mm
H1, H2, H3, H4: MountingHole; MountingHole_3mm
J1: B4B-XH-A-BK_LF__SN_; B4BXHABKLFSN
J2: USB_C_Receptacle_USB2.0_14P; USB_C_Receptacle_Molex_105450-0101
L1: B82472P6472M000; INDPM7373X450N
R1: 7.5K; R_0603_1608Metric_Pad0.98x0.95mm_HandSolder
R2: 10; R_0603_1608Metric_Pad0.98x0.95mm_HandSolder
R3: 1K; R_0603_1608Metric
R4: 10K; R_0603_1608Metric
SW1, SW2, SW3: SW_Omron_B3FS; SW_SPST_Omron_B3FS-100xP
U1: AP63205WU; TSOT-23-6
U2: TMC5130A-TA; TQFP-48-1EP_7x7mm_P0.5mm_EP5x5mm_ThermalVias
U3: CH224K; SSOP-10-1EP_3.9x4.9mm_P1mm_EP2.1x3.3mm

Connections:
+3.3V: A1.36 (3V3), C8.2, C11.2, U2.10 (VCC_IO), U2.12 (SPI_MODE)
+5V: A1.40 (VBUS), C4.2, C5.2, C9.1, D1.1 (VDD), L1.2, R1.2, R2.1, U1.1 (FB)
/cpu/GPIO20: A1.26 (GPIO20), U2.29 (~DRV_EN_CFG6)
/cpu/NEOPIXEL: A1.5 (GPIO3), D1.4 (DIN)
/cpu/OA1: J1.4, U2.46 (OA1)
/cpu/OA2: J1.3, U2.42 (OA2)
/cpu/OB1: J1.2, U2.15 (OB1)
/cpu/OB2: J1.1, U2.19 (OB2)
/cpu/SW_DIST: A1.4 (GPIO2), SW3.2
/cpu/SW_PULL: A1.2 (GPIO1), SW2.2
/cpu/SW_PUSH: A1.1 (GPIO0), SW1.2
/cpu/clk: A1.24 (SPI0_SCK), U2.4 (SCK_CFG2)
/cpu/rx: A1.21 (SPI0_RX), U2.7 (SDO_NAO_CFG0)
/cpu/tx: A1.25 (SPI0_TX), U2.5 (SDI_NAI_CFG1)
/cpu/~csn: A1.22 (~SPI0_CSn), U2.3 (~CS_CFG3)
GND: A1.3 (GND), A1.8 (GND), A1.13 (GND), A1.18 (GND), A1.23 (GND), A1.28 (GND), A1.33 (GND), A1.38 (GND), A1.D2 (GND), C1.1, C2.1, C4.1, C5.1, C8.1, C9.2, C10.1, C11.1, C12.1, C13.2, C14.1, D1.3 (VSS), J2.A1 (GND), J2.A12 (GND), J2.B1 (GND), J2.B12 (GND), SW1.1, SW2.1, SW3.1, U1.4 (GND), U2.1 (TST_MODE), U2.2 (CLK), U2.6 (NC), U2.11 (SD_MODE), U2.13 (GNDP), U2.17 (BRB), U2.28 (SWSEL), U2.31 (NC), U2.32 (GNDA), U2.36 (NC), U2.44 (BRA), U2.48 (GNDP), U2.49 (EP), U3.2 (CFG2), U3.9 (CFG1), U3.11 (GND)
unnamed: J2.A5 (CC1), U3.7 (CC1)
unnamed: J2.B5 (CC2), U3.6 (CC2)
unnamed: C3.2, L1.1, U1.6 (BST)
unnamed: C3.1, U1.5 (SW)
unnamed: C12.2, U2.33 (5VOUT)
unnamed: R1.1, U2.30 (AIN_IREF)
unnamed: C7.1, U2.35 (CP0)
unnamed: C7.2, U2.37 (CPI)
unnamed: C10.2, R2.2, U2.34 (VCC)
unnamed: C6.2, U2.38 (VCP)
unnamed: C14.2, R3.2, U3.1 (VDD), U3.3 (CFG3)
unnamed: J2.A7 (D-), J2.B7 (D-), U3.5 (DM)
unnamed: J2.A6 (D+), J2.B6 (D+), U3.4 (DP)
unnamed: R4.2, U3.8 (VBUS)
VCC: C1.2, C2.2, C6.1, C13.1, J2.A4 (VBUS), J2.A9 (VBUS), J2.B4 (VBUS), J2.B9 (VBUS), R3.1, R4.1, U1.2 (EN), U1.3 (IN), U2.21 (VS), U2.39 (VSA), U2.40 (VS)

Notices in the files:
tests/fixtures/run23/tigard_placed.kicad_pcb:
Copyright Franklin Harding 2020
Licensed under CC-BY-SA 4.0
